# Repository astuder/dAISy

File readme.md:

dAISy - A simple DIY AIS Receiver
=================================

dAISy (do AIS yourself) is a simple AIS receiver based on Silicon Labs [Si4362 EZRadioPro](https://www.silabs.com/wireless/proprietary/ezradiopro-sub-ghz-ics/device.si4362) receiver, Texas Instruments [MSP430G2553](http://www.ti.com/product/msp430g2553) MCU and [MSP-EXP430G2](http://www.ti.com/tool/msp-exp430g2) v1.5 LaunchPad. The software was developed with Code Composer Studio 5.5.

AIS, short for "Automatic Identification System", is a tracking system for ships. More on [Wikipedia](http://en.wikipedia.org/wiki/Automatic_Identification_System). There are many websites dedicated to tracking ships based on this system, like for example [MarineTraffic](http://www.marinetraffic.com/).

dAISy features:
- integrated radio, no need for external radio with discriminator tap
- hopping between channel A (161.975 MHz) and B (162.025 MHz)
- receives, decodes and validates packets according to ITU-R M.1371-4 (NRZI decoding, bit-destuffing, CRC validation) 
- wraps valid packets into NMEA 0183 sentences (AIVDM)
- sends NMEA sentences to PC via serial (9600 8N1)

The output of dAISy can be processed and visualized by mapping and navigation programs like [OpenCPN](http://opencpn.org).

All content of this project is published under CC BY-SA - [Creative Commons Attribution-ShareAlike](http://creativecommons.org/licenses/by-sa/4.0/).  

A more detailed description of the project can be found in the [43oh.com forum](http://forum.43oh.com/topic/4833-potm-daisy-a-simple-ais-receiver/).

For those that just want the finished product: I sell the big sisters of dAISy in our [web store](https://shop.wegmatt.com).

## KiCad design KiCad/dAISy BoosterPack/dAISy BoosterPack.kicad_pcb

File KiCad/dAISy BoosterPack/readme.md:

Breakout board for the Si446x as MSP430 BoosterPack. 

Paired with a [TI MSP430F5529 LaunchPad](https://www.ti.com/tool/MSP-EXP430F5529LP), this board can also be used with the (closed source) [dAISy USB firmware](https://github.com/astuder/dAISy/tree/master/Firmware).

This breakout board is also the basis of [this project](https://github.com/NSwiz1/msp430-si4467-ais-audio-receiver), which uses the Raw or Sync data from the Si446x for audio input into ShipPlotter software.

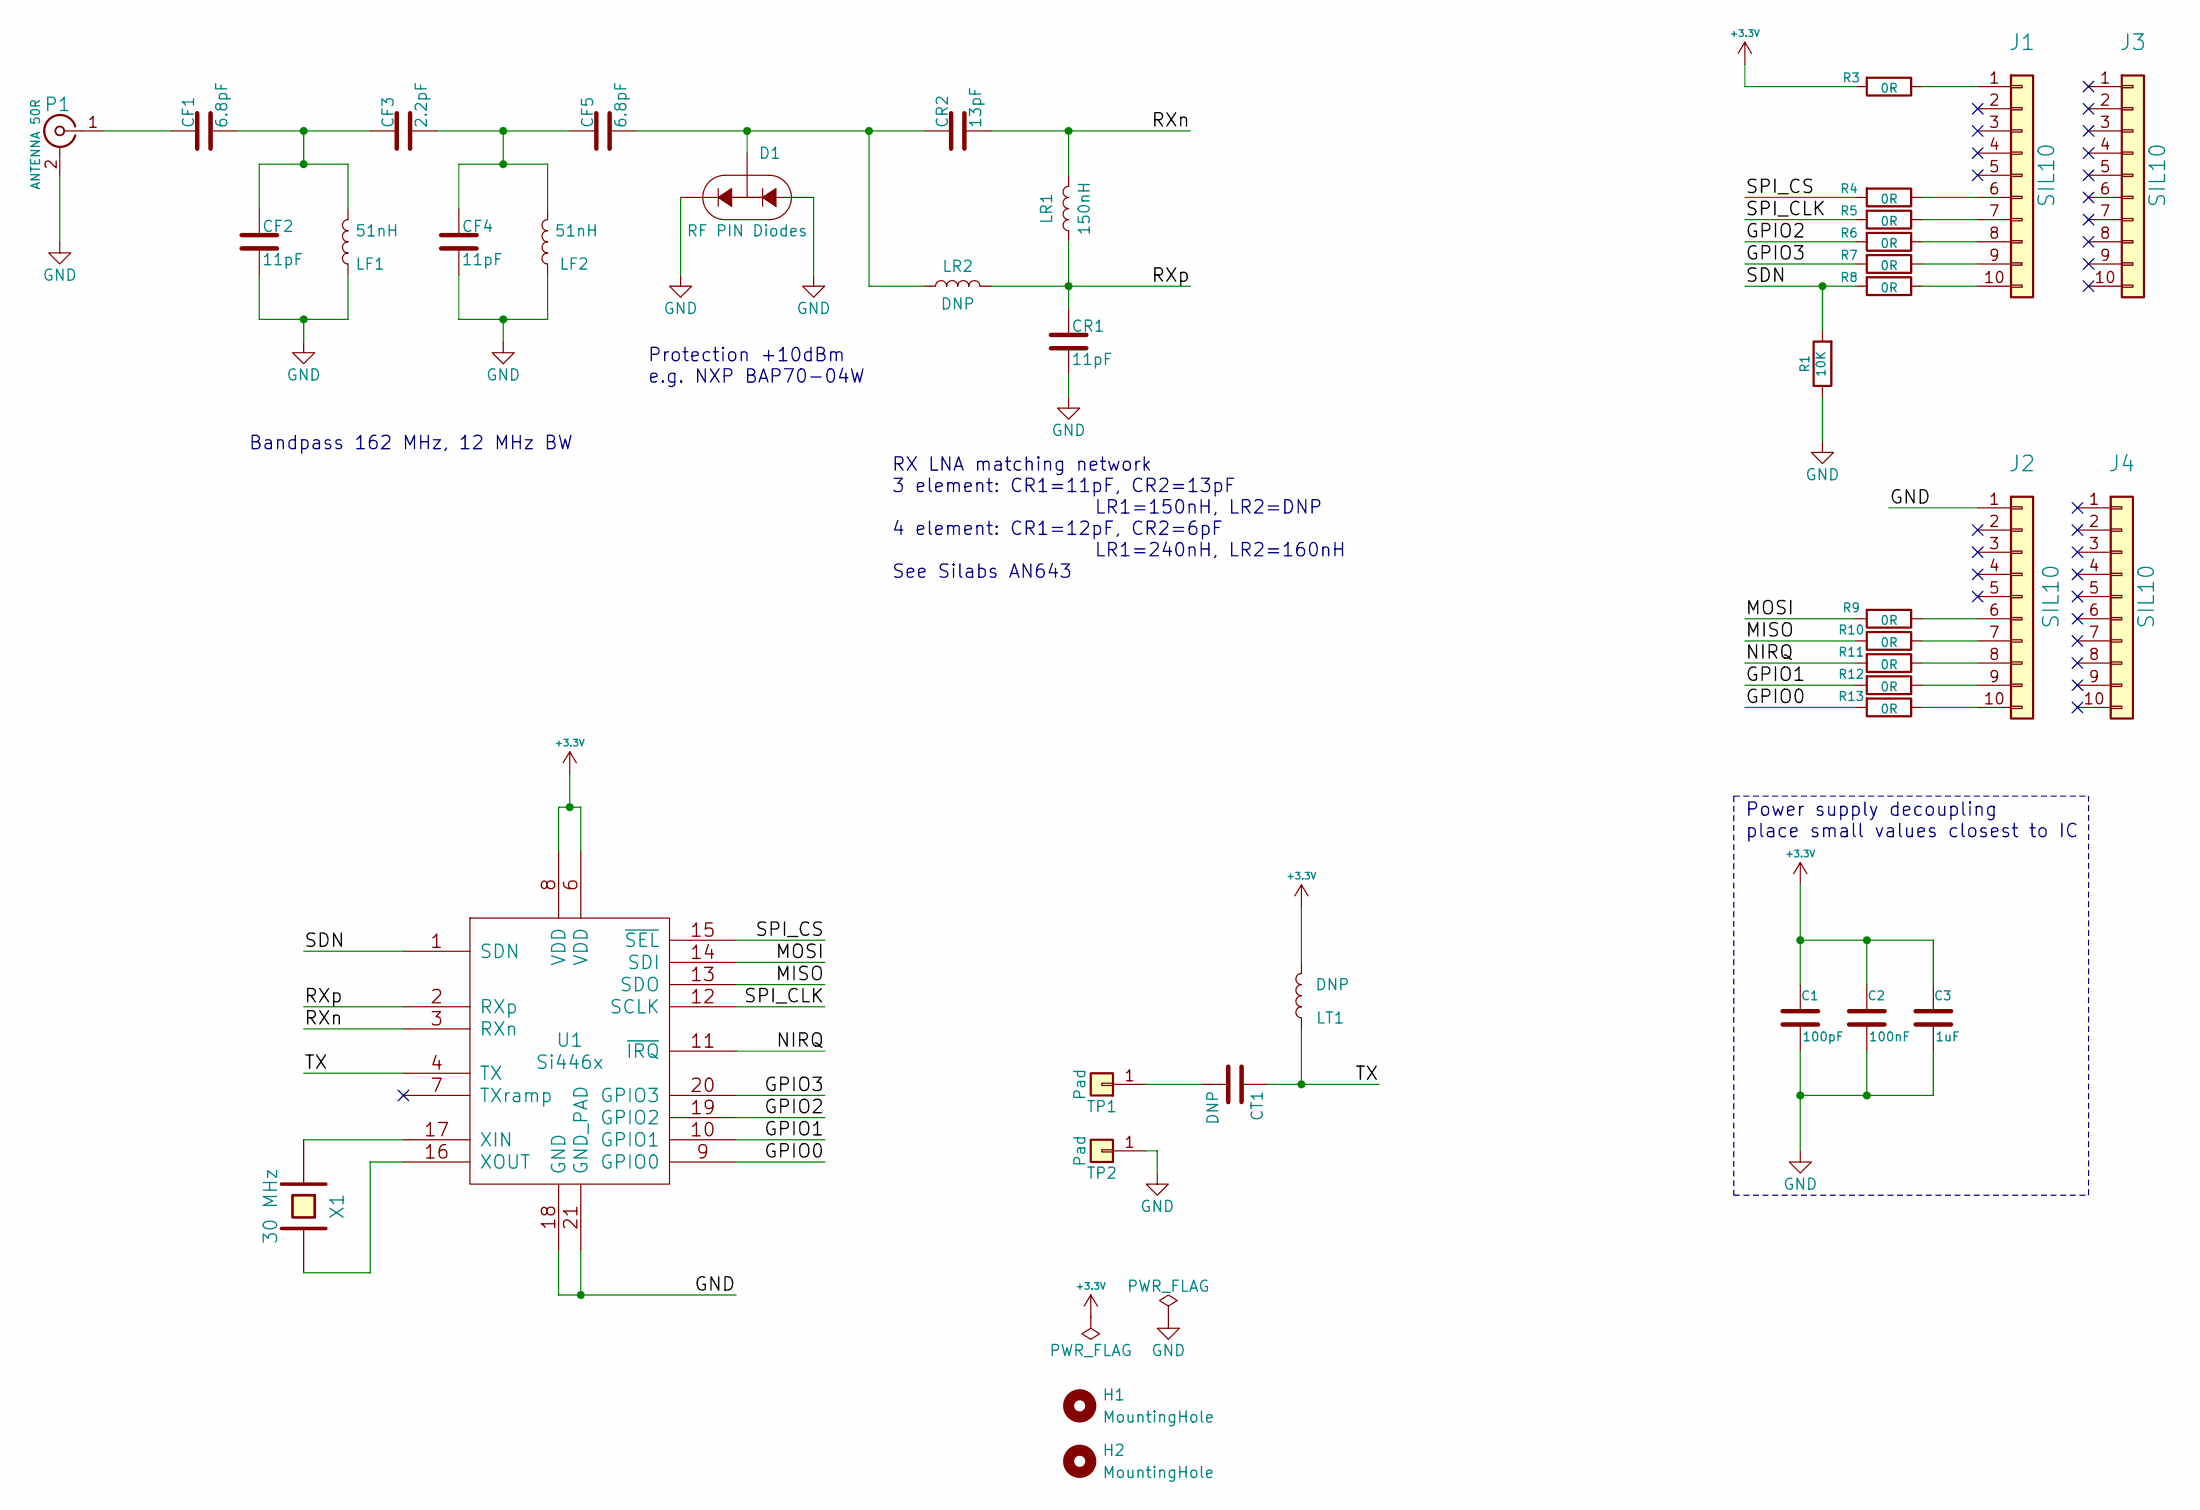
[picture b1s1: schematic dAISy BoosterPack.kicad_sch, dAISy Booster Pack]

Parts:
C1: 100pF; C_0603_1608Metric_Pad1.08x0.95mm_HandSolder
C2: 100nF; C_0603_1608Metric_Pad1.08x0.95mm_HandSolder
C3: 1uF; C_0603_1608Metric_Pad1.08x0.95mm_HandSolder
CF1, CF5: 6.8pF; C_0603_1608Metric_Pad1.08x0.95mm_HandSolder
CF2, CF4: 11pF; C_0603_1608Metric_Pad1.08x0.95mm_HandSolder
CF3: 2.2pF; C_0603_1608Metric_Pad1.08x0.95mm_HandSolder
CR1: 11pF; C_0603_1608Metric_Pad1.08x0.95mm_HandSolder
CR2: 13pF; C_0603_1608Metric_Pad1.08x0.95mm_HandSolder
CT1: DNP; C_0603_1608Metric_Pad1.08x0.95mm_HandSolder
D1: RF PIN Diodes; SOT-323_SC-70_Handsoldering
H1, H2: MountingHole; MountingHole_2.5mm
J1, J2: SIL10; SIL-10-W
J3, J4: SIL10; SIL-10-W-no-silk
LF1, LF2: 51nH; C_0603_1608Metric_Pad1.08x0.95mm_HandSolder
LR1: 150nH; C_0603_1608Metric_Pad1.08x0.95mm_HandSolder
LR2: DNP; C_0603_1608Metric_Pad1.08x0.95mm_HandSolder
LT1: DNP; C_0603_1608Metric_Pad1.08x0.95mm_HandSolder
P1: ANTENNA 50R; BNC_Molex_73138-5033
R1: 10K; R_0603_1608Metric_Pad0.98x0.95mm_HandSolder
R3, R4, R5, R6, R7, R8, R9, R10, R11, R12, R13: 0R; R_0603_1608Metric_Pad0.98x0.95mm_HandSolder
TP1, TP2: Pad; TestPoint_THTPad_D1.5mm_Drill0.7mm
U1: Si446x; QFN-20_long_pads
X1: 30 MHz; Crystal-32x25

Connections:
+3.3V: C1.1, C2.1, C3.1, LT1.2, R3.2, U1.6 (VDD), U1.8 (VDD)
/GPIO0: R13.2, U1.9 (GPIO0)
/GPIO1: R12.2, U1.10 (GPIO1)
/GPIO2: R6.2, U1.19 (GPIO2)
/GPIO3: R7.2, U1.20 (GPIO3)
/MISO: R10.2, U1.13 (SDO)
/MOSI: R9.2, U1.14 (SDI)
/NIRQ: R11.2, U1.11 (~IRQ)
/RXn: CR2.2, LR1.2, U1.3 (RXn)
/RXp: CR1.1, LR1.1, LR2.2, U1.2 (RXp)
/SDN: R1.2, R8.2, U1.1 (SDN)
/SPI_CLK: R5.2, U1.12 (SCLK)
/SPI_CS: R4.2, U1.15 (~SEL)
/TX: CT1.1, LT1.1, U1.4 (TX)
GND: C1.2, C2.2, C3.2, CF2.2, CF4.2, CR1.2, D1.1, D1.2, J2.1, LF1.1, LF2.1, P1.2 (Ext), R1.1, TP2.1, U1.18 (GND), U1.21 (GND_PAD), X1.2 (GND)
unnamed: CF1.2, CF2.1, CF3.1, LF1.2
unnamed: CF3.2, CF4.1, CF5.1, LF2.2
unnamed: CF5.2, CR2.1, D1.3, LR2.1
unnamed: J1.1, R3.1
unnamed: J1.6, R4.1
unnamed: J1.7, R5.1
unnamed: J1.8, R6.1
unnamed: J1.9, R7.1
unnamed: J1.10, R8.1
unnamed: J2.6, R9.1
unnamed: J2.7, R10.1
unnamed: J2.8, R11.1
unnamed: J2.9, R12.1
unnamed: J2.10, R13.1
unnamed: CF1.1, P1.1 (In)
unnamed: CT1.2, TP1.1
unnamed: U1.17 (XIN), X1.1
unnamed: U1.16 (XOUT), X1.3

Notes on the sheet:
Bandpass 162 MHz, 12 MHz BW
RX LNA matching network 3 element: CR1=11pF, CR2=13pF LR1=150nH, LR2=DNP 4 element: CR1=12pF, CR2=6pF LR1=240nH, LR2=160nH See Silabs AN643
Power supply decoupling place small values closest to IC
Protection +10dBm e.g. NXP BAP70-04W

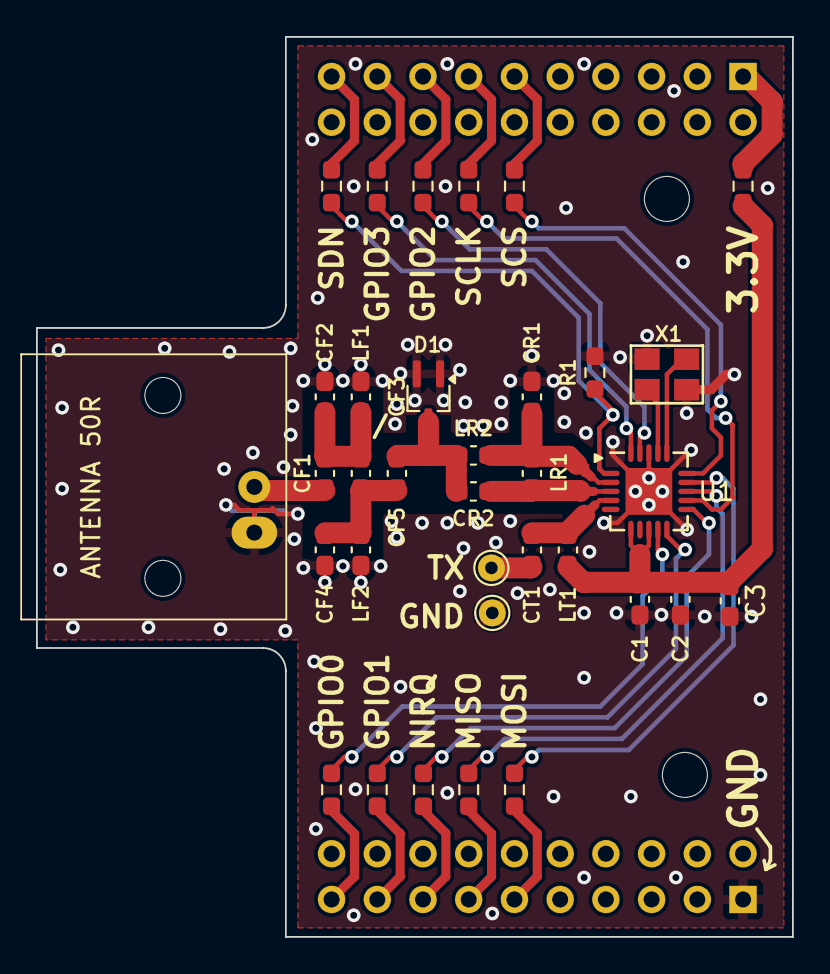
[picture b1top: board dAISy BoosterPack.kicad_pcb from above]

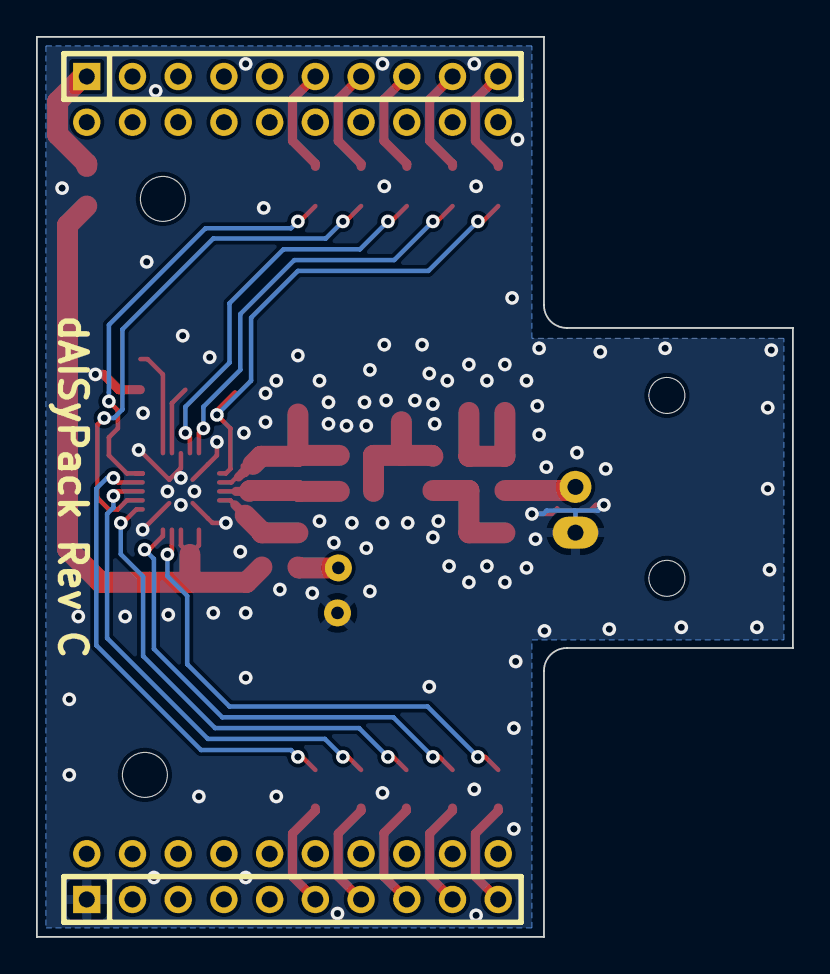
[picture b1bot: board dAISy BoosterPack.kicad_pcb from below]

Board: 2 copper layers, 42.0 x 50.0 mm, 40 parts (4 on the bottom side), 33 nets.

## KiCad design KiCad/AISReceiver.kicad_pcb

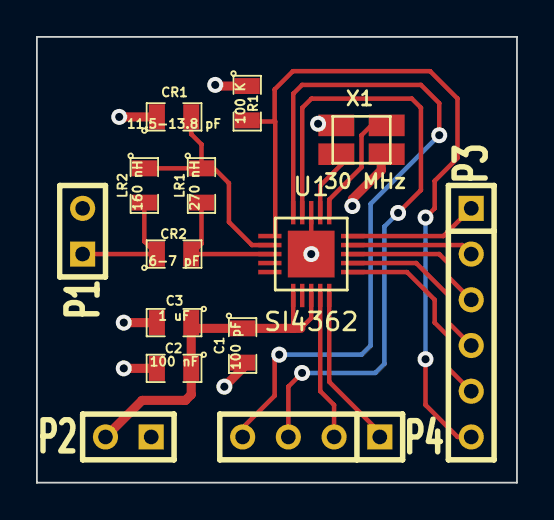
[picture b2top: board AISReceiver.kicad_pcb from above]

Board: 2 copper layers, 26.7 x 24.8 mm, 14 parts (0 on the bottom side), 17 nets.

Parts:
C1: 100 pF; SM0805
C2: 100 nF; SM0805
C3: 1 uF; SM0805
CR1: 11.5-13.8 pF; SM0805
CR2: 6-7 pF; SM0805
LR1: 270 nH; SM0805
LR2: 160 nH; SM0805
P1: Antenna; SIL-2
P2: Power; SIL-2
P3: SPI; SIL-6
P4: GPIO; SIL-4
R1: 100 K; SM0805
U1: SI4362; QFN20+1
X1: 30 MHz; crystal_FA238-TSX3225

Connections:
/GPIO2: P4.3, U1.19
/GPIO3: P4.4, U1.20
/SDN: P3.6, R1.2, U1.1
GND: C1.2, C2.2, C3.2, CR1.1, P1.2, P2.1, R1.1, U1.18, U1.21, X1.3
unnamed: P3.5, U1.11
unnamed: P3.4, U1.12
unnamed: P3.3, U1.13
unnamed: P3.2, U1.14
unnamed: P3.1, U1.15
unnamed: P4.2, U1.9
unnamed: P4.1, U1.10
unnamed: U1.16, X1.2
unnamed: U1.17, X1.1
unnamed: C1.1, C2.1, C3.1, P2.2, U1.6, U1.8
unnamed: CR1.2, LR1.1, LR2.1, U1.2
unnamed: CR2.1, LR2.2, P1.1
unnamed: CR2.2, LR1.2, U1.3

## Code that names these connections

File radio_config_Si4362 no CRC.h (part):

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/*
// Command:                  RF_GPIO_PIN_CFG
// Description:              Configures the GPIO pins.
//                           GPIO0: 0x1A = SYNC_WORD_DETECTED	(1 when sync word detected, back to 0 when end of packet)
//                           GPIO1: 0x00 = DEFAULT = CTS
//                           GPIO2: 0x11 = RX_DATA_CLK
//                           GPIO3: 0x14 = RX_DATA
//                           NIRQ:  0x27 = CCA		(1 when RSSI threshold exceeded detected, back to 0 when below threshold) - 0x00 = DEFAULT = IRQ (active low)
//                           SDO:   0x00 = DEFAULT = SDO (SPI data out)
*/
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
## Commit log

2013-11-13 Project created
2013-11-13 IRQ on DATA_CLK and NRZI
2013-11-17 AIS-24 refactored packet handler into separate file
2013-12-16 code to test packet handler w/o radio
2013-12-16 AIS-21 data receive state machine
2013-12-18 AIS-6: Calculate and verify CRC
    incl. extended test routine
    incl. fixing code to match conventions
2013-12-19 AIS-22 implemented FIFO for storing packets
    incl. test code to verify FIFO operation
2013-12-19 basic control logic for testing w/ radio
2013-12-23 additional test code for verification
    includes first snippets to parse AIS message, NMEA encoding, output of
    decimal strings
2013-12-23 AIS-13 implemented basic serial out
    plus some cleanup in SPI lib
2013-12-24 AIS-25 AIS-26 NMEA processing
    send received packets as NMEA sentences over UART
2013-12-24 more detailed description
2013-12-24 updated links
2013-12-24 typos
2013-12-24 code clean-up
2013-12-24 fixed missing UART init
    added more debug code
2013-12-24 clear last error when read
2013-12-24 more logging
2013-12-25 bugfix: increase NMEA fragment count
2013-12-25 Added copyright notice
2013-12-25 add reference to thread on 43oh.com
2013-12-28 hardware schematic (KiCad)
2013-12-31 preemptive volatile
2014-01-06 Updated radio configuration
    Using latest version of WDS tool (3.2.5.0), added configuration file to
    project
2014-01-06 Channel Hopping
    implemented channel hopping, added IR calibration, plus some refactoring
2014-01-06 Saleae Logic configuration
2014-01-06 decreased time between channel hops
2014-01-06 updated description
2014-01-06 fix for radio hanging
    using radio in Direct RX, i.e. disabled hardware packet handler as it
    might interfere with software implementation. added some debug LED code
    to packet handler
2014-01-13 bug fixes and LPM
    tested and fixed AIS, shortened preamble to 12 bits, rolled back radio
    configuration to known-good state, put MCU into LPM4
2014-01-15 moved radio control into ph isr
2014-01-15 inlined SPI transfer
2014-01-15 optimized reading RSSI through FRR, additional inlining
2014-01-20 new preamble and start flag processing #5
2014-01-23 add RSSI evaluation to packet handler, closes #2
2014-01-23 add remark re external radio
2014-01-25 fixed error reporting
2014-02-02 missing RSSI defines
2014-02-02 Rev B schematic and layout
2014-02-05 create HEX file for release builds
2014-06-03 Support for Si446x based on E10-M4463D module.
2014-06-04 account for radio channel byte
2014-06-16 synced packed handler with dAISy USB
2014-06-16 4463 direct rx radio config
2014-06-16 4463 WDS configuration
2014-06-16 changed radio config to direct RX
2014-06-16 added RADIO_PORT define
2014-06-16 removed old configuration file
2014-07-13 added Kicad library cache
2014-09-20 rewired for new boosterpack
2014-11-09 IR calibration according to AN790
2015-02-23 fixed preamble to start flag transition
2015-02-23 updated CCS configuration to ignore Kicad folder
2015-05-18 added refence to Tindie
2015-08-19 adding dAISy USB firmware packages
2015-08-19 smaller picture
2015-08-19 fixing firmware readme
2015-08-19 updated CCS project configuration
2015-08-20 clarified readme
2015-08-23 added direct firmware links
2015-08-23 fixed direct firmware links
2015-08-23 fixes
2015-09-07 firmware update 4.03
2015-09-07 readme formatting
2015-10-15 firmware update 4.04
2015-11-21 create folder for old FW
2015-11-21 clarify hardware version 2 description
2015-11-21 clarify upgrade procedure
2015-11-21 add link to terminal program instructions
2016-03-13 add error check for too empty message
2016-03-14 Add note about when update is not needed
2016-05-30 new firmware 4.08
2016-05-30 update documentation
2016-05-30 updated documentation for fw 4.08
2016-06-13 Add instructions for un-bricking dAISy
2016-06-13 update links
2016-06-13 fix anchor
2016-12-06 Provide firmware as ZIP file
2017-01-25 Release of dAISy USB firmware 4.11
2017-01-25 fixed mark-up
2017-12-24 Firmware 4.14
2018-01-02 Clarified devices to which this firmware applies
2018-02-22 Avoid unicode characters in path
2018-04-09 add images
2019-04-20 Config file for WDS 3.2.11.0
2021-11-14 dAISy USB firmware 4.15
2021-11-14 fixed F5502 picture
2021-11-14 changed target to link
2021-11-14 formatting
2022-02-24 changed license to CC BY-SA (removed NC)
2022-04-18 fixed link to Silabs website
    https://www.silabs.com/wireless/proprietary/ezradiopro-sub-ghz-ics/device.si4362
2026-03-20 add dAISy BoosterPack KiCad project
2026-03-21 link to dAISy BoosterPack design files
2026-04-08 add readme for BoosterPack
    Added image and additional project details to readme.
2026-04-08 Fix image path in readme.md
    Updated image path for dAISyPack in readme.

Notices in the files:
radio_config_Si4362 no CRC.h:
@n Copyright 2013 Silicon Laboratories, Inc.
